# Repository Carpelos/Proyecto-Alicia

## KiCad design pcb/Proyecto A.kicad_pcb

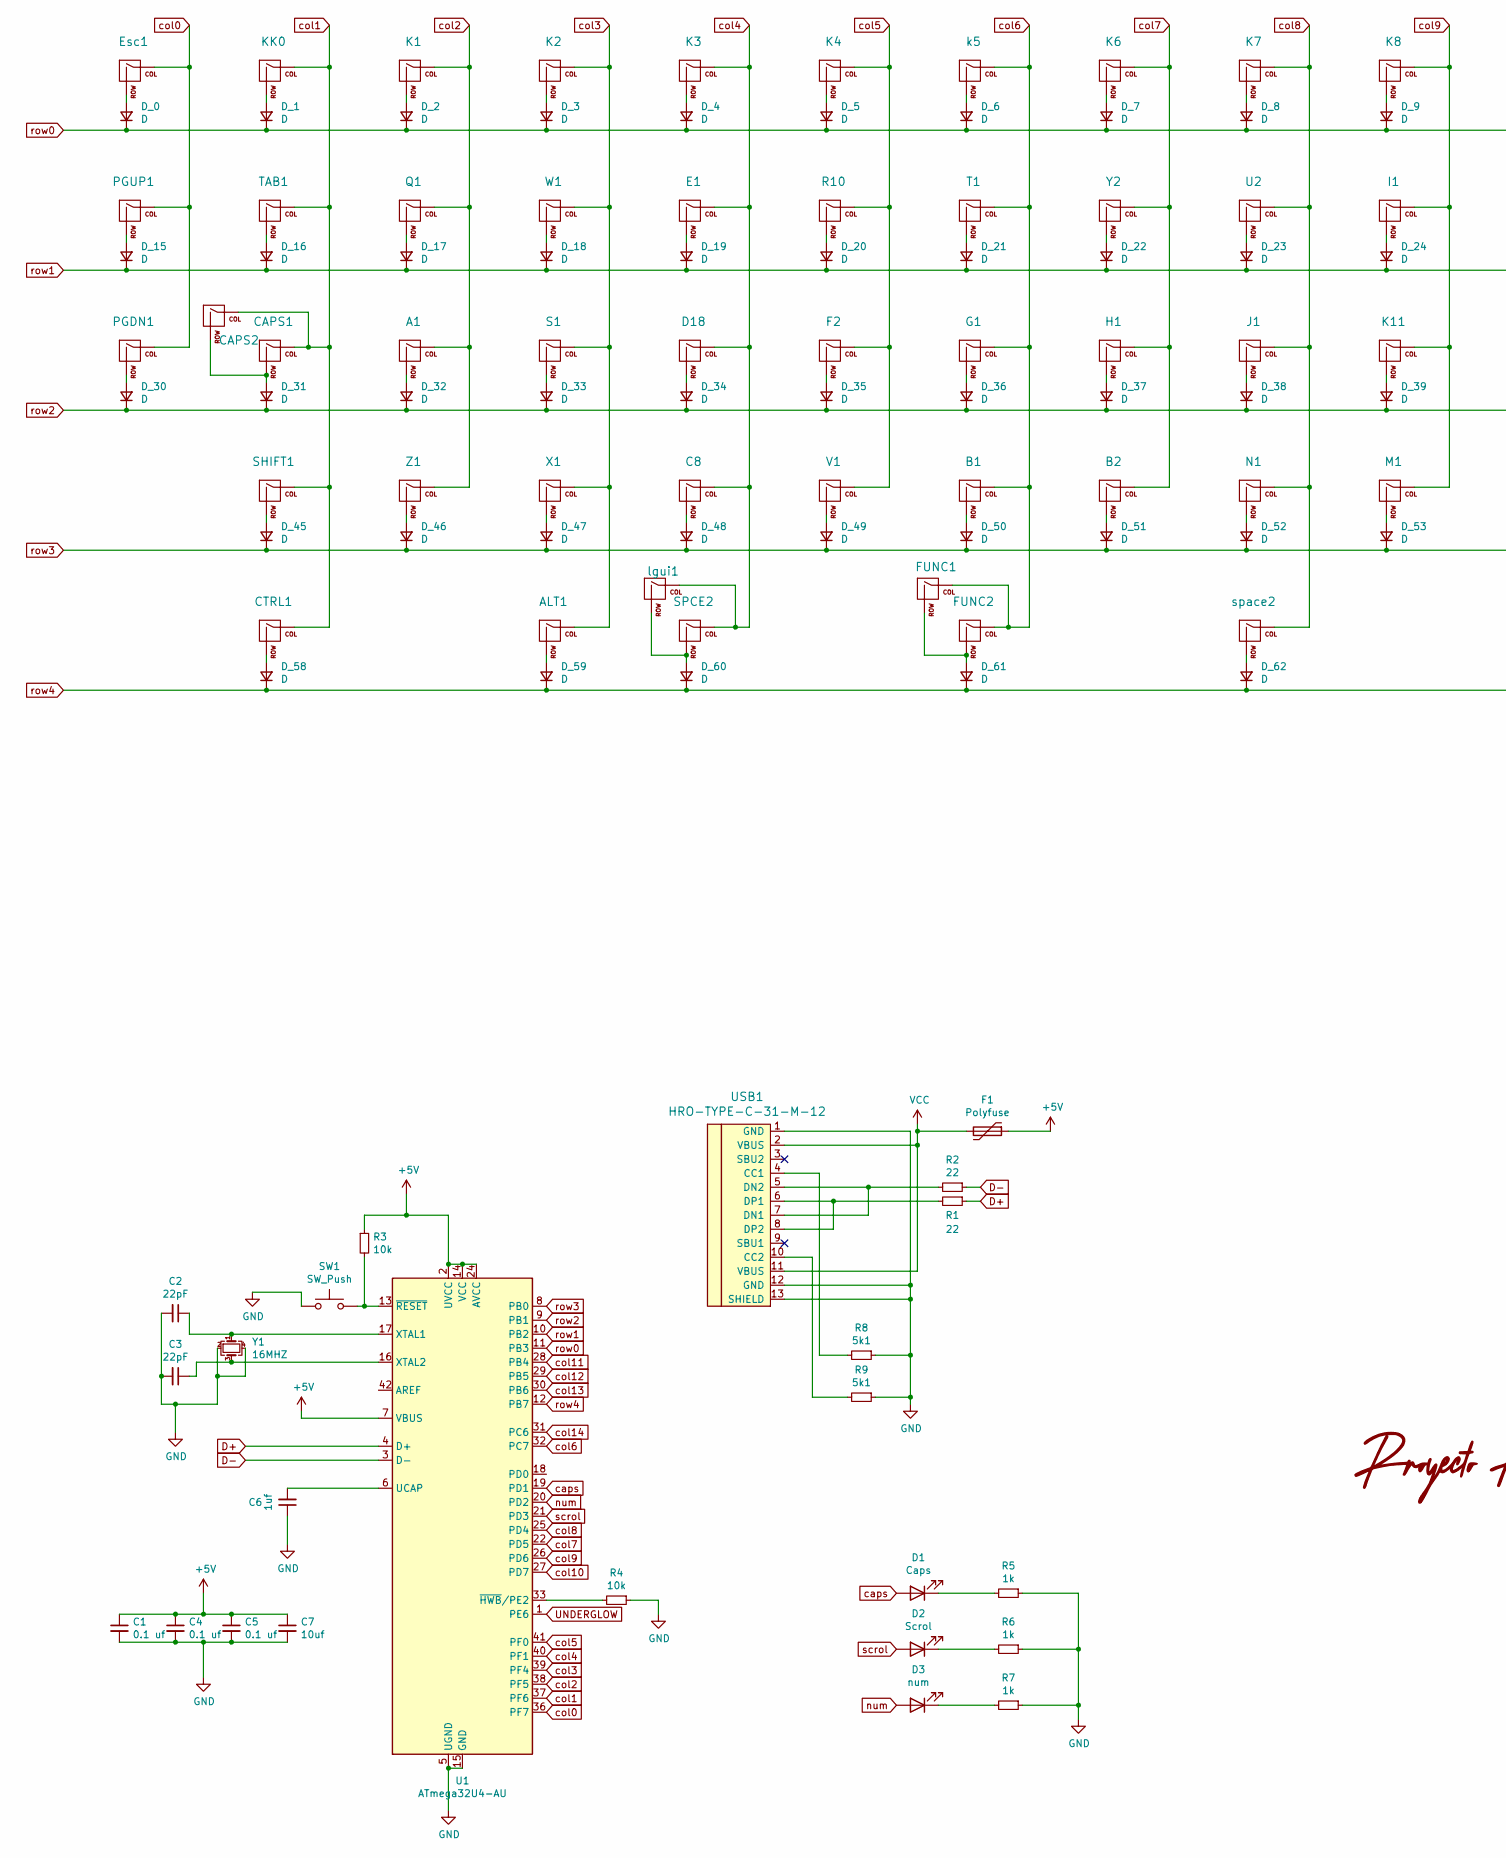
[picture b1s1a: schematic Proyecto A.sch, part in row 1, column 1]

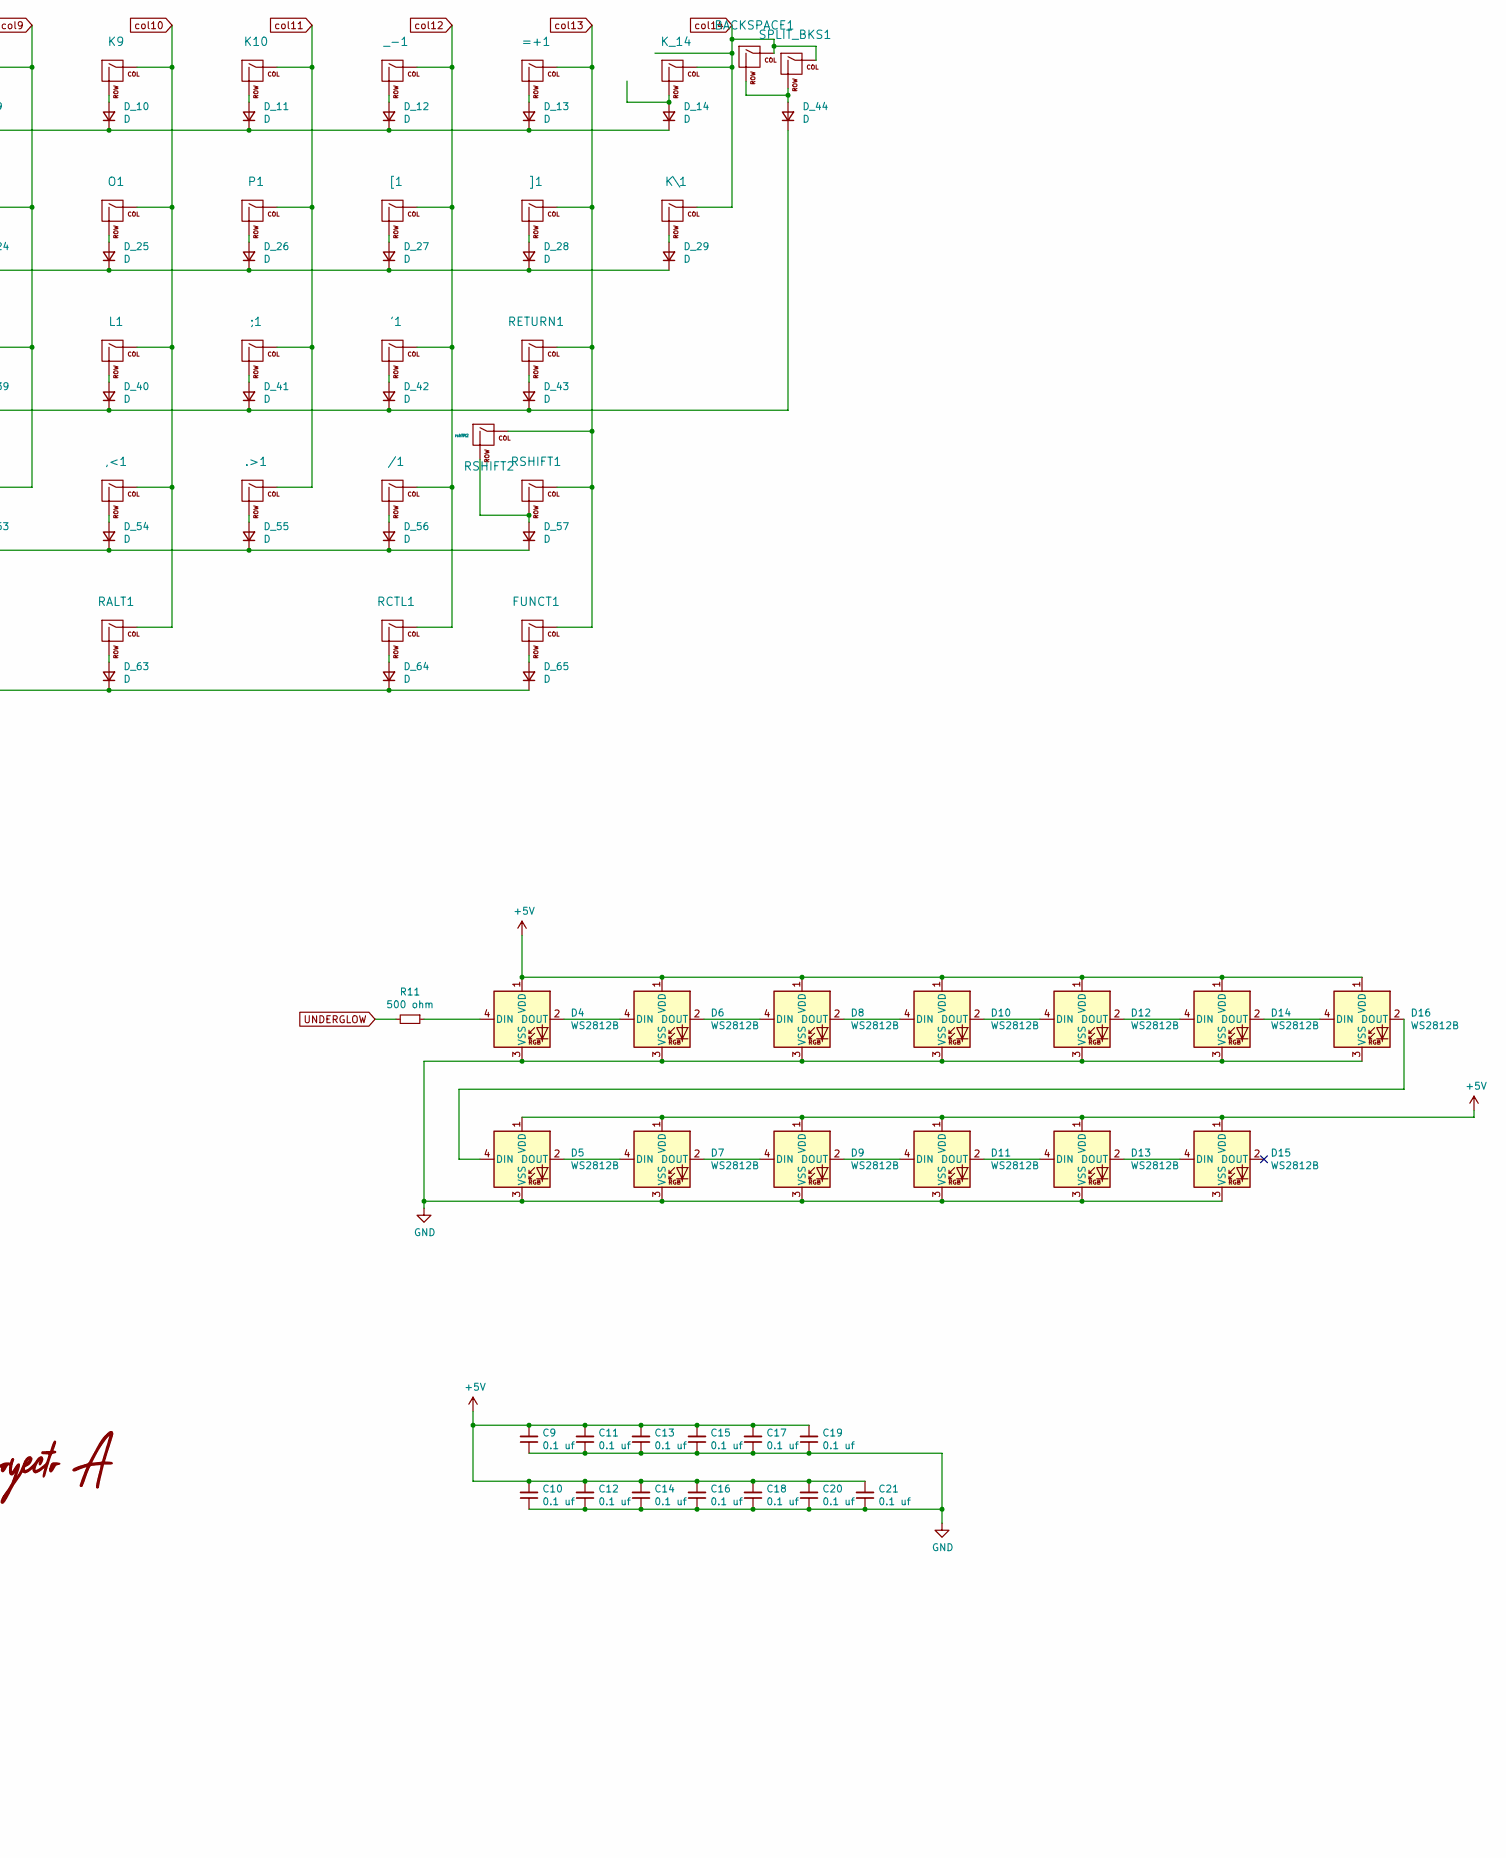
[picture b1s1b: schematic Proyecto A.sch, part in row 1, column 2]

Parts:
'1: '; MXOnly-1U-NoLED
,<1: ,<; MXOnly-1U-NoLED
.>1: .>; MXOnly-1U-NoLED
/1: /; MXOnly-1U-NoLED
;1: ;; MXOnly-1U-NoLED
=+1: =; MXOnly-1U-NoLED
A1: a; MXOnly-1U-NoLED
ALT1: lalt; MXOnly-1.5U-NoLED
B1: b; MXOnly-1U-NoLED
B2: b2; MXOnly-1U-NoLED
BACKSPACE1: backspace; MXOnly-2U-NoLED
C1, C4, C5, C9, C10, C11, C12, C13, C14, C15, C16, C17, C18, C19, C20, C21: 0.1 uf; C_0805_2012Metric_Pad1.15x1.40mm_HandSolder
C2, C3: 22pF; C_0805_2012Metric_Pad1.15x1.40mm_HandSolder
C6: 1uf; C_0805_2012Metric_Pad1.15x1.40mm_HandSolder
C7: 10uf; C_0805_2012Metric_Pad1.15x1.40mm_HandSolder
C8: c; MXOnly-1U-NoLED
CAPS1: caps1; MXOnly-1.75U-NoLED
CAPS2: stcaps; MXOnly-1U-NoLED
CTRL1: lctrl; MXOnly-1.5U-NoLED
D1: Caps; LED_1206_3216Metric_Pad1.42x1.75mm_HandSolder
D2: Scrol; LED_1206_3216Metric_Pad1.42x1.75mm_HandSolder
D3: num; LED_1206_3216Metric_Pad1.42x1.75mm_HandSolder
D4, D5, D6, D7, D8, D9, D10, D11, D12, D13, D14, D15, D16: WS2812B; LED_WS2812B_PLCC4_5.0x5.0mm_P3.2mm
D18: d; MXOnly-1U-NoLED
D_0, D_1, D_2, D_3, D_4, D_5, D_6, D_7, D_8, D_9, D_10, D_11, D_12, D_13, D_14, D_15, D_16, D_17, D_18, D_19, D_20, D_21, D_22, D_23, D_24, D_25, D_26, D_27, D_28, D_29, D_30, D_31, D_32, D_33, D_34, D_35, D_36, D_37, D_38, D_39, D_40, D_41, D_42, D_43, D_44, D_45, D_46, D_47, D_48, D_49, D_50, D_51, D_52, D_53, D_54, D_55, D_56, D_57, D_58, D_59, D_60, D_61, D_62, D_63, D_64, D_65: D; D_SOD-123; JLC C64898
E1: e; MXOnly-1U-NoLED
Esc1: KEYSW; MXOnly-1U-NoLED
F1: Polyfuse; Fuse_1206_3216Metric
F2: f; MXOnly-1U-NoLED
FUNC1: func1; MXOnly-1U-NoLED
FUNC2: func1-2; MXOnly-1.25U-NoLED
FUNCT1: FUNC3; MXOnly-1U-NoLED
G1: g; MXOnly-1U-NoLED
H1: h; MXOnly-1U-NoLED
I1: i; MXOnly-1U-NoLED
J1: j; MXOnly-1U-NoLED
K1: 1; MXOnly-1U-NoLED
K2: 2; MXOnly-1U-NoLED
K3: 3; MXOnly-1U-NoLED
K4: 4; MXOnly-1U-NoLED
K6: 6; MXOnly-1U-NoLED
K7: 7; MXOnly-1U-NoLED
K8: 8; MXOnly-1U-NoLED
K9: 9; MXOnly-1U-NoLED
K10: 10; MXOnly-1U-NoLED
K11: k; MXOnly-1U-NoLED
KK0: ES; MXOnly-1U-NoLED
K\1: \\|; MXOnly-1U-NoLED
K_14: sbackspace; MXOnly-1U-NoLED
L1: l; MXOnly-1U-NoLED
M1: KEYSW; MXOnly-1U-NoLED
N1: n; MXOnly-1U-NoLED
O1: o; MXOnly-1U-NoLED
P1: p; MXOnly-1U-NoLED
PGDN1: KEYSW; MXOnly-1U-NoLED
PGUP1: pgup; MXOnly-1U-NoLED
Q1: q; MXOnly-1U-NoLED
R1, R2: 22; R_0805_2012Metric
R3, R4: 10k; R_0805_2012Metric
R5, R6, R7: 1k; R_0805_2012Metric
R8, R9: 5k1; R_0805_2012Metric
R10: r; MXOnly-1U-NoLED
R11: 500 ohm; R_0805_2012Metric_Pad1.15x1.40mm_HandSolder
RALT1: ralt; MXOnly-1.5U-NoLED
RCTL1: RCTRL; MXOnly-1.5U-NoLED
RETURN1: return; MXOnly-2.25U-ReversedStabilizers-NoLED
RSHIFT1: rshift1; MXOnly-1.75U-NoLED
RSHIFT2: rshift2; MXOnly-2.75U-NoLED
S1: s; MXOnly-1U-NoLED
SHIFT1: lshift; MXOnly-2.25U-NoLED
SPCE2: lgui2; MXOnly-2U-ReversedStabilizers-NoLED
SPLIT_BKS1: sbbackspace2; MXOnly-1U-NoLED
SW1: SW_Push; SW_SPST_SKQG_WithStem
T1: t; MXOnly-1U-NoLED
TAB1: tabulador; MXOnly-1.5U-NoLED
U1: ATmega32U4-AU; TQFP-44_10x10mm_P0.8mm
U2: u; MXOnly-1U-NoLED
USB1: HRO-TYPE-C-31-M-12; HRO-TYPE-C-31-M-12-HandSoldering
V1: v; MXOnly-1U-NoLED
W1: w; MXOnly-1U-NoLED
X1: x; MXOnly-1U-NoLED
Y1: 16MHZ; Crystal_SMD_3225-4Pin_3.2x2.5mm_HandSoldering
Y2: y; MXOnly-1U-NoLED
Z1: z; MXOnly-1U-NoLED
[1: [; MXOnly-1U-NoLED
]1: ]; MXOnly-1U-NoLED
_-1: -; MXOnly-1U-NoLED
k5: 5; MXOnly-1U-NoLED
lgui1: lgui; MXOnly-2.25U-ReversedStabilizers-NoLED
space2: KEYSW; MXOnly-2.75U-ReversedStabilizers-NoLED

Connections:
+5V: C1.1, C4.1, C5.1, C7.1, C9.2, C10.2, C11.2, C12.2, C13.2, C14.2, C15.2, C16.2, C17.2, C18.2, C19.2, C20.2, C21.2, D4.1 (VDD), D5.1 (VDD), D6.1 (VDD), D7.1 (VDD), D8.1 (VDD), D9.1 (VDD), D10.1 (VDD), D11.1 (VDD), D12.1 (VDD), D13.1 (VDD), D14.1 (VDD), D15.1 (VDD), D16.1 (VDD), F1.1, R3.1, U1.2 (UVCC), U1.7 (VBUS), U1.14 (VCC), U1.24 (AVCC), U1.34 (VCC), U1.44 (AVCC)
D+: R1.1, U1.4 (D+)
D-: R2.1, U1.3 (D-)
GND: C1.2, C2.2, C3.2, C4.2, C5.2, C6.1, C7.2, C9.1, C10.1, C11.1, C12.1, C13.1, C14.1, C15.1, C16.1, C17.1, C18.1, C19.1, C20.1, C21.1, D4.3 (VSS), D5.3 (VSS), D6.3 (VSS), D7.3 (VSS), D8.3 (VSS), D9.3 (VSS), D10.3 (VSS), D11.3 (VSS), D12.3 (VSS), D13.3 (VSS), D14.3 (VSS), D15.3 (VSS), D16.3 (VSS), R4.1, R5.1, R6.1, R7.1, R8.1, R9.1, SW1.1, U1.5 (UGND), U1.15 (GND), U1.23 (GND), U1.35 (GND), U1.43 (GND), USB1.1 (GND), USB1.12 (GND), USB1.13 (SHIELD), Y1.2, Y1.4
unnamed: '1.2 (ROW), D_42.2 (A)
unnamed: ,<1.2 (ROW), D_54.2 (A)
unnamed: .>1.2 (ROW), D_55.2 (A)
unnamed: /1.2 (ROW), D_56.2 (A)
unnamed: ;1.2 (ROW), D_41.2 (A)
unnamed: =+1.2 (ROW), D_13.2 (A)
unnamed: A1.2 (ROW), D_32.2 (A)
unnamed: ALT1.2 (ROW), D_59.2 (A)
unnamed: B1.2 (ROW), D_50.2 (A)
unnamed: B2.2 (ROW), D_51.2 (A)
unnamed: BACKSPACE1.2 (ROW), D_44.2 (A), SPLIT_BKS1.2 (ROW)
unnamed: C2.1, U1.17 (XTAL1), Y1.1
unnamed: C3.1, U1.16 (XTAL2), Y1.3
unnamed: C6.2, U1.6 (UCAP)
unnamed: C8.2 (ROW), D_48.2 (A)
unnamed: CAPS1.2 (ROW), CAPS2.2 (ROW), D_31.2 (A)
unnamed: CTRL1.2 (ROW), D_58.2 (A)
unnamed: D1.1 (K), R5.2
unnamed: D2.1 (K), R6.2
unnamed: D3.1 (K), R7.2
unnamed: D4.2 (DOUT), D6.4 (DIN)
unnamed: D4.4 (DIN), R11.1
unnamed: D5.2 (DOUT), D7.4 (DIN)
unnamed: D6.2 (DOUT), D8.4 (DIN)
unnamed: D7.2 (DOUT), D9.4 (DIN)
unnamed: D10.2 (DOUT), D12.4 (DIN)
unnamed: D8.2 (DOUT), D10.4 (DIN)
unnamed: D11.2 (DOUT), D13.4 (DIN)
unnamed: D9.2 (DOUT), D11.4 (DIN)
unnamed: D12.2 (DOUT), D14.4 (DIN)
unnamed: D13.2 (DOUT), D15.4 (DIN)
unnamed: D14.2 (DOUT), D16.4 (DIN)
unnamed: D5.4 (DIN), D16.2 (DOUT)
unnamed: D18.2 (ROW), D_34.2 (A)
unnamed: D_0.2 (A), Esc1.2 (ROW)
unnamed: D_1.2 (A), KK0.2 (ROW)
unnamed: D_2.2 (A), K1.2 (ROW)
unnamed: D_3.2 (A), K2.2 (ROW)
unnamed: D_4.2 (A), K3.2 (ROW)
unnamed: D_5.2 (A), K4.2 (ROW)
unnamed: D_6.2 (A), k5.2 (ROW)
unnamed: D_7.2 (A), K6.2 (ROW)
unnamed: D_8.2 (A), K7.2 (ROW)
unnamed: D_9.2 (A), K8.2 (ROW)
unnamed: D_10.2 (A), K9.2 (ROW)
unnamed: D_11.2 (A), K10.2 (ROW)
unnamed: D_12.2 (A), _-1.2 (ROW)
unnamed: D_14.2 (A), K_14.2 (ROW)
unnamed: D_15.2 (A), PGUP1.2 (ROW)
unnamed: D_16.2 (A), TAB1.2 (ROW)
unnamed: D_17.2 (A), Q1.2 (ROW)
unnamed: D_18.2 (A), W1.2 (ROW)
unnamed: D_19.2 (A), E1.2 (ROW)
unnamed: D_20.2 (A), R10.2 (ROW)
unnamed: D_21.2 (A), T1.2 (ROW)
unnamed: D_22.2 (A), Y2.2 (ROW)
unnamed: D_23.2 (A), U2.2 (ROW)
unnamed: D_24.2 (A), I1.2 (ROW)
unnamed: D_25.2 (A), O1.2 (ROW)
unnamed: D_26.2 (A), P1.2 (ROW)
unnamed: D_27.2 (A), [1.2 (ROW)
unnamed: D_28.2 (A), ]1.2 (ROW)
unnamed: D_29.2 (A), K\1.2 (ROW)
unnamed: D_30.2 (A), PGDN1.2 (ROW)
unnamed: D_33.2 (A), S1.2 (ROW)
unnamed: D_35.2 (A), F2.2 (ROW)
unnamed: D_36.2 (A), G1.2 (ROW)
unnamed: D_37.2 (A), H1.2 (ROW)
unnamed: D_38.2 (A), J1.2 (ROW)
unnamed: D_39.2 (A), K11.2 (ROW)
unnamed: D_40.2 (A), L1.2 (ROW)
unnamed: D_43.2 (A), RETURN1.2 (ROW)
unnamed: D_45.2 (A), SHIFT1.2 (ROW)
unnamed: D_46.2 (A), Z1.2 (ROW)
unnamed: D_47.2 (A), X1.2 (ROW)
unnamed: D_49.2 (A), V1.2 (ROW)
unnamed: D_52.2 (A), N1.2 (ROW)
unnamed: D_53.2 (A), M1.2 (ROW)
unnamed: D_57.2 (A), RSHIFT1.2 (ROW), RSHIFT2.2 (ROW)
unnamed: D_60.2 (A), SPCE2.2 (ROW), lgui1.2 (ROW)
unnamed: D_61.2 (A), FUNC1.2 (ROW), FUNC2.2 (ROW)
unnamed: D_62.2 (A), space2.2 (ROW)
unnamed: D_63.2 (A), RALT1.2 (ROW)
unnamed: D_64.2 (A), RCTL1.2 (ROW)
unnamed: D_65.2 (A), FUNCT1.2 (ROW)
unnamed: R1.2, USB1.6 (DP1), USB1.8 (DP2)
unnamed: R2.2, USB1.5 (DN2), USB1.7 (DN1)
unnamed: R3.2, SW1.2, U1.13 (~RESET)
unnamed: R4.2, U1.33 (~HWB~/PE2)
unnamed: R8.2, USB1.4 (CC1)
unnamed: R9.2, USB1.10 (CC2)
UNDERGLOW: R11.2, U1.1 (PE6)
VCC: F1.2, USB1.2 (VBUS), USB1.11 (VBUS)
caps: D1.2 (A), U1.19 (PD1)
col0: Esc1.1 (COL), PGDN1.1 (COL), PGUP1.1 (COL), U1.36 (PF7)
col1: CAPS1.1 (COL), CAPS2.1 (COL), CTRL1.1 (COL), KK0.1 (COL), SHIFT1.1 (COL), TAB1.1 (COL), U1.37 (PF6)
col2: A1.1 (COL), K1.1 (COL), Q1.1 (COL), U1.38 (PF5), Z1.1 (COL)
col3: ALT1.1 (COL), K2.1 (COL), S1.1 (COL), U1.39 (PF4), W1.1 (COL), X1.1 (COL)
col4: C8.1 (COL), D18.1 (COL), E1.1 (COL), K3.1 (COL), SPCE2.1 (COL), U1.40 (PF1), lgui1.1 (COL)
col5: F2.1 (COL), K4.1 (COL), R10.1 (COL), U1.41 (PF0), V1.1 (COL)
col6: B1.1 (COL), FUNC1.1 (COL), FUNC2.1 (COL), G1.1 (COL), T1.1 (COL), U1.32 (PC7), k5.1 (COL)
col7: B2.1 (COL), H1.1 (COL), K6.1 (COL), U1.22 (PD5), Y2.1 (COL)
col8: J1.1 (COL), K7.1 (COL), N1.1 (COL), U1.25 (PD4), U2.1 (COL), space2.1 (COL)
col9: I1.1 (COL), K8.1 (COL), K11.1 (COL), M1.1 (COL), U1.26 (PD6)
col10: ,<1.1 (COL), K9.1 (COL), L1.1 (COL), O1.1 (COL), RALT1.1 (COL), U1.27 (PD7)
col11: .>1.1 (COL), ;1.1 (COL), K10.1 (COL), P1.1 (COL), U1.28 (PB4)
col12: '1.1 (COL), /1.1 (COL), RCTL1.1 (COL), U1.29 (PB5), [1.1 (COL), _-1.1 (COL)
col13: =+1.1 (COL), FUNCT1.1 (COL), RETURN1.1 (COL), RSHIFT1.1 (COL), RSHIFT2.1 (COL), U1.30 (PB6), ]1.1 (COL)
col14: BACKSPACE1.1 (COL), K\1.1 (COL), K_14.1 (COL), SPLIT_BKS1.1 (COL), U1.31 (PC6)
num: D3.2 (A), U1.20 (PD2)
row0: D_0.1 (K), D_1.1 (K), D_2.1 (K), D_3.1 (K), D_4.1 (K), D_5.1 (K), D_6.1 (K), D_7.1 (K), D_8.1 (K), D_9.1 (K), D_10.1 (K), D_11.1 (K), D_12.1 (K), D_13.1 (K), D_14.1 (K), U1.11 (PB3)
row1: D_15.1 (K), D_16.1 (K), D_17.1 (K), D_18.1 (K), D_19.1 (K), D_20.1 (K), D_21.1 (K), D_22.1 (K), D_23.1 (K), D_24.1 (K), D_25.1 (K), D_26.1 (K), D_27.1 (K), D_28.1 (K), D_29.1 (K), U1.10 (PB2)
row2: D_30.1 (K), D_31.1 (K), D_32.1 (K), D_33.1 (K), D_34.1 (K), D_35.1 (K), D_36.1 (K), D_37.1 (K), D_38.1 (K), D_39.1 (K), D_40.1 (K), D_41.1 (K), D_42.1 (K), D_43.1 (K), D_44.1 (K), U1.9 (PB1)
row3: D_45.1 (K), D_46.1 (K), D_47.1 (K), D_48.1 (K), D_49.1 (K), D_50.1 (K), D_51.1 (K), D_52.1 (K), D_53.1 (K), D_54.1 (K), D_55.1 (K), D_56.1 (K), D_57.1 (K), U1.8 (PB0)
row4: D_58.1 (K), D_59.1 (K), D_60.1 (K), D_61.1 (K), D_62.1 (K), D_63.1 (K), D_64.1 (K), D_65.1 (K), U1.12 (PB7)
scrol: D2.2 (A), U1.21 (PD3)

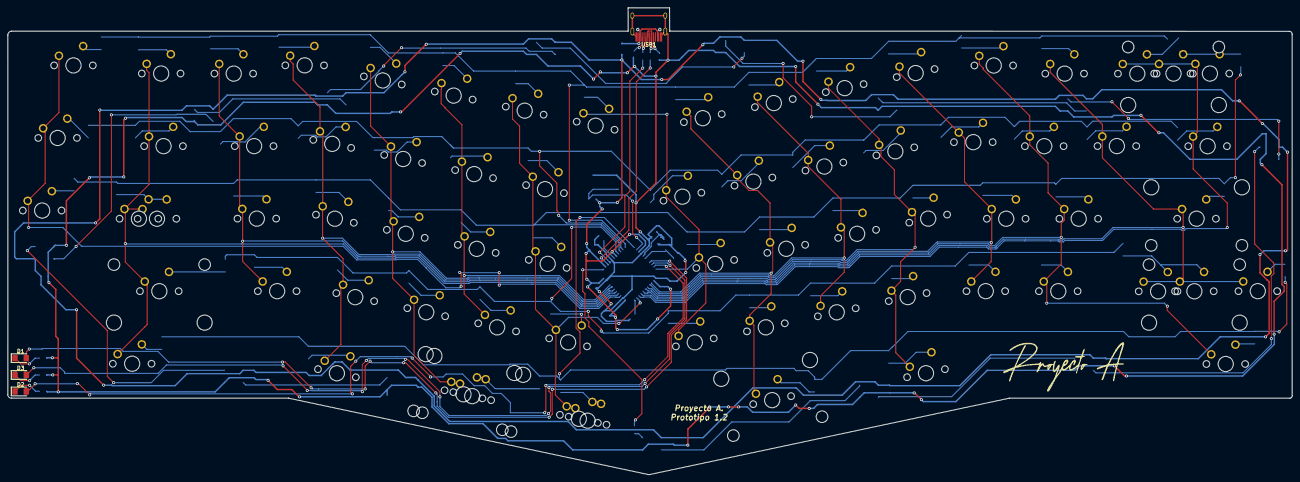
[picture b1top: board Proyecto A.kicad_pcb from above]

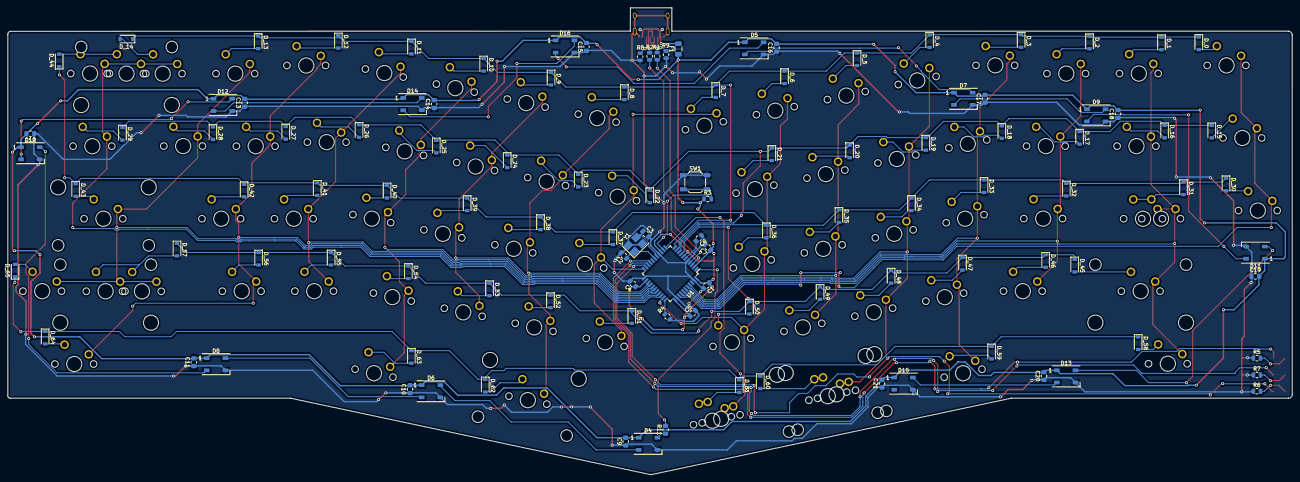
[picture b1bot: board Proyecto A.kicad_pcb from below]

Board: 2 copper layers, 337.3 x 122.6 mm, 188 parts (113 on the bottom side), 120 nets.

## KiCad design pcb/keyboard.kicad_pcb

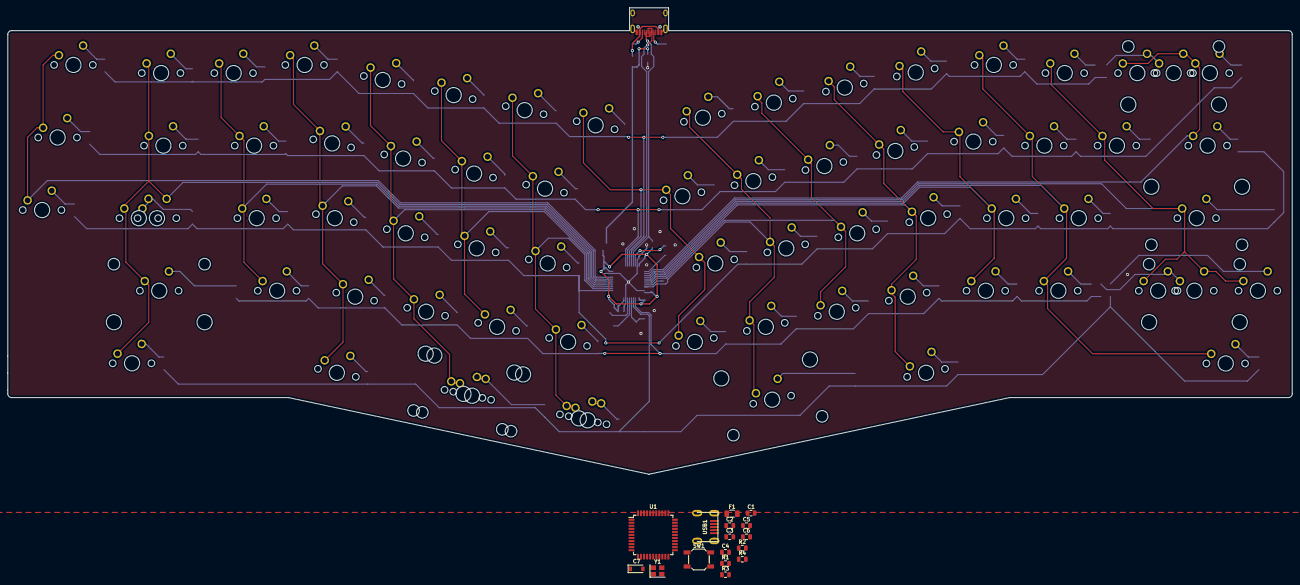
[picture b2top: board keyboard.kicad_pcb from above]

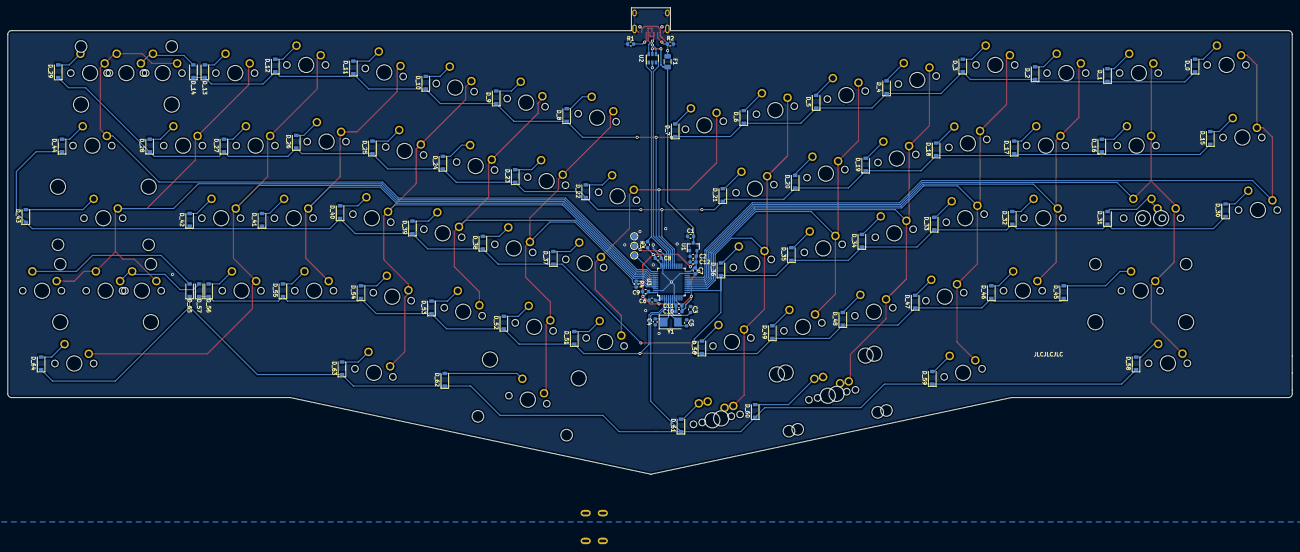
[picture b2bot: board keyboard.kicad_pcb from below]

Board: 2 copper layers, 337.2 x 122.5 mm, 178 parts (90 on the bottom side), 108 nets.

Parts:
C1, C4, C5: 0.1 uf; C_0805_2012Metric
C1#2, C2#2, C10: 1u; C_0603_1608Metric
C2, C3: 22pF; C_0805_2012Metric
C3#2, C6#2, C7#2, C8, C9, C11: 100n; C_0603_1608Metric
C4#2, C5#2: 20p; C_0603_1608Metric
C6: C_Small; C_0805_2012Metric
C7: 100uf; D_SOD-123
C12: 10u; C_0603_1608Metric
D_0, D_1, D_2, D_3, D_4, D_5, D_6, D_7, D_8, D_9, D_10, D_11, D_12, D_13, D_14, D_15, D_16, D_17, D_18, D_19, D_20, D_21, D_22, D_23, D_24, D_25, D_26, D_27, D_28, D_29, D_30, D_31, D_32, D_33, D_34, D_35, D_36, D_37, D_38, D_39, D_40, D_41, D_42, D_43, D_44, D_45, D_46, D_47, D_48, D_49, D_50, D_51, D_52, D_53, D_54, D_55, D_56, D_57, D_58, D_59, D_60, D_61, D_62, D_63, D_64, D_65: D; D_SOD-123
F1: Polyfuse; Fuse_1206_3216Metric
F1#2: 500mA; Fuse_1206_3216Metric
J1, J2, J3: Conn_01x01_Female; TestPoint_Pad_D1.5mm
K_0, K_1, K_2, K_3, K_4, K_5, K_6, K_7, K_8, K_9, K_10, K_11, K_12, K_13, K_14, K_15, K_17, K_18, K_19, K_20, K_21, K_22, K_23, K_24, K_25, K_26, K_27, K_28, K_29, K_30, K_32, K_33, K_34, K_35, K_36, K_37, K_38, K_39, K_40, K_41, K_42, K_46, K_47, K_48, K_49, K_50, K_51, K_52, K_53, K_54, K_55, K_56, K_65: KEYSW; MXOnly-1U-NoLED
K_16, K_44, K_58, K_59, K_63, K_64: KEYSW; MXOnly-1.5U-NoLED
K_31, K_57: KEYSW; MXOnly-1.75U-NoLED
K_43: KEYSW; MXOnly-2.25U-ReversedStabilizers-NoLED
K_45: KEYSW; MXOnly-2.25U-NoLED
K_60: KEYSW; MXOnly-2U-ReversedStabilizers-NoLED
K_61: KEYSW; MXOnly-1.25U-NoLED
K_62: KEYSW; MXOnly-2.75U-ReversedStabilizers-NoLED
K_142: MX-NoLED; MXOnly-2U-NoLED
K_312, K_612: MX-NoLED; MXOnly-1U-NoLED
K_572: MX-NoLED; MXOnly-2.75U-NoLED
K_602: MX-NoLED; MXOnly-2.25U-ReversedStabilizers-NoLED
R1, R2: 22; Fuse_0805_2012Metric
R1#2, R2#2: 5.1k; R_0603_1608Metric
R3: R_Small; Fuse_0805_2012Metric
R3#2: 1.5k; R_0603_1608Metric
R4: 10k; Fuse_0805_2012Metric
R4#2: 10k; R_0603_1608Metric
SW1: SW_Push; SW_SPST_SKQG_WithStem
U1: ATmega32U4-AU; TQFP-44_10x10mm_P0.8mm
U1#2: XC6206P332MR; SOT-23
U2: SRV05-4; SOT-23-6
U3: STM32F103C8Tx; LQFP-48_7x7mm_P0.5mm
USB1: Molex-0548190589
USB1#2: HRO-TYPE-C-31-M-12; HRO-TYPE-C-31-M-12-jlc
Y1: 16MHZ; Crystal_SMD_3225-4Pin_3.2x2.5mm
Y1#2: 8MHz; Crystal_SMD_5032-2Pin_5.0x3.2mm

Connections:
+5V: C1.1, C1#2.2, C4.1, C5.1, C7.1, F1.1, F1#2.1, R3.1, U1.2, U1.7, U1.14, U1.24, U1.34, U1.44, U1#2.3, U2.5
/VBUS: F1#2.2, USB1#2.2, USB1#2.11
BOOT0: R4#2.1, U3.44
D+: R2.2, R3#2.2, U2.6, U3.33, USB1.3, USB1#2.6, USB1#2.8
D-: R1.2, U2.4, U3.32, USB1.4, USB1#2.5, USB1#2.7
GND: C1.2, C1#2.1, C2.2, C2#2.2, C3.2, C3#2.2, C4.2, C4#2.2, C5.2, C5#2.2, C6.1, C6#2.2, C7.2, C7#2.2, C8.2, C9.2, C10.2, C11.2, C12.2, J3.1, R1#2.1, R2#2.1, R4.1, R4#2.2, SW1.1, U1.5, U1.15, U1.23, U1.35, U1.43, U1#2.1, U2.2, U3.8, U3.23, U3.35, U3.47, USB1.1, USB1#2.1, USB1#2.12, USB1#2.13, Y1.2, Y1.4
NRST: C3#2.1, U3.7
unnamed: C2.1, U1.17, Y1.1
unnamed: C3.1, U1.16, Y1.3
unnamed: C4#2.1, U3.5, Y1#2.1
unnamed: C5#2.1, U3.6, Y1#2.2
unnamed: C6.2, U1.6
unnamed: D_0.2, K_0.2
unnamed: D_1.2, K_1.2
unnamed: D_2.2, K_2.2
unnamed: D_3.2, K_3.2
unnamed: D_4.2, K_4.2
unnamed: D_5.2, K_5.2
unnamed: D_6.2, K_6.2
unnamed: D_7.2, K_7.2
unnamed: D_8.2, K_8.2
unnamed: D_9.2, K_9.2
unnamed: D_10.2, K_10.2
unnamed: D_11.2, K_11.2
unnamed: D_12.2, K_12.2
unnamed: D_13.2, K_13.2
unnamed: D_14.2, K_14.2, K_142.1
unnamed: D_15.2, K_15.2
unnamed: D_16.2, K_16.2
unnamed: D_17.2, K_17.2
unnamed: D_18.2, K_18.2
unnamed: D_19.2, K_19.2
unnamed: D_20.2, K_20.2
unnamed: D_21.2, K_21.2
unnamed: D_22.2, K_22.2
unnamed: D_23.2, K_23.2
unnamed: D_24.2, K_24.2
unnamed: D_25.2, K_25.2
unnamed: D_26.2, K_26.2
unnamed: D_27.2, K_27.2
unnamed: D_28.2, K_28.2
unnamed: D_29.2, K_29.2
unnamed: D_30.2, K_30.2
unnamed: D_31.2, K_31.2, K_312.1
unnamed: D_32.2, K_32.2
unnamed: D_33.2, K_33.2
unnamed: D_34.2, K_34.2
unnamed: D_35.2, K_35.2
unnamed: D_36.2, K_36.2
unnamed: D_37.2, K_37.2
unnamed: D_38.2, K_38.2
unnamed: D_39.2, K_39.2
unnamed: D_40.2, K_40.2
unnamed: D_41.2, K_41.2
unnamed: D_42.2, K_42.2
unnamed: D_43.2, K_43.2
unnamed: D_44.2, K_44.2
unnamed: D_45.2, K_45.2
unnamed: D_46.2, K_46.2
unnamed: D_47.2, K_47.2
unnamed: D_48.2, K_48.2
unnamed: D_49.2, K_49.2
unnamed: D_50.2, K_50.2
unnamed: D_51.2, K_51.2
unnamed: D_52.2, K_52.2
unnamed: D_53.2, K_53.2
unnamed: D_54.2, K_54.2
unnamed: D_55.2, K_55.2
unnamed: D_56.2, K_56.2
unnamed: D_57.2, K_57.2, K_572.1
unnamed: D_58.2, K_58.2
unnamed: D_59.2, K_59.2
unnamed: D_60.2, K_60.2, K_602.2
unnamed: D_61.2, K_61.2, K_612.2
unnamed: D_62.2, K_62.2
unnamed: D_63.2, K_63.2
unnamed: D_64.2, K_64.2
unnamed: D_65.2, K_65.2
unnamed: R1.1, U1.3
unnamed: R1#2.2, USB1#2.4
unnamed: R2.1, U1.4
unnamed: R2#2.2, USB1#2.10
unnamed: R3.2, SW1.2, U1.13
unnamed: R4.2, U1.33
SWDCLK: J2.1, U3.37
SWDIO: J1.1, U3.34
VBAT: C2#2.1, C6#2.1, C7#2.1, C8.1, C9.1, C10.1, C11.1, C12.1, R3#2.1, U1#2.2, U3.1, U3.9, U3.24, U3.36, U3.48
VCC: F1.2, USB1.5
col0: K_0.1, K_15.1, K_30.1, U3.21
col1: K_1.1, K_16.1, K_31.1, K_45.1, K_58.1, K_312.2, U3.20
col2: K_2.1, K_17.1, K_32.1, K_46.1, U3.19
col3: K_3.1, K_18.1, K_33.1, K_47.1, K_59.1, U3.18
col4: K_4.1, K_19.1, K_34.1, K_48.1, K_60.1, K_602.1, U3.17
col5: K_5.1, K_20.1, K_35.1, K_49.1, U3.16
col6: K_6.1, K_21.1, K_36.1, K_50.1, K_61.1, K_612.1, U3.15
col7: K_7.1, K_22.1, K_37.1, K_51.1, U3.30
col8: K_8.1, K_23.1, K_38.1, K_52.1, K_62.1, U3.45
col9: K_9.1, K_24.1, K_39.1, K_53.1, U3.43
col10: K_10.1, K_25.1, K_40.1, K_54.1, K_63.1, U3.42
col11: K_11.1, K_26.1, K_41.1, K_55.1, U3.41
col12: K_12.1, K_27.1, K_42.1, K_56.1, K_64.1, U3.40
col13: K_13.1, K_28.1, K_43.1, K_57.1, K_65.1, K_572.2, U3.39
col14: K_14.1, K_29.1, K_44.1, K_142.2, U3.38
row0: D_0.1, D_1.1, D_2.1, D_3.1, D_4.1, D_5.1, D_6.1, D_7.1, D_8.1, D_9.1, D_10.1, D_11.1, D_12.1, D_13.1, D_14.1, U3.31
row1: D_15.1, D_16.1, D_17.1, D_18.1, D_19.1, D_20.1, D_21.1, D_22.1, D_23.1, D_24.1, D_25.1, D_26.1, D_27.1, D_28.1, D_29.1, U3.29
row2: D_30.1, D_31.1, D_32.1, D_33.1, D_34.1, D_35.1, D_36.1, D_37.1, D_38.1, D_39.1, D_40.1, D_41.1, D_42.1, D_43.1, D_44.1, U3.14
row3: D_45.1, D_46.1, D_47.1, D_48.1, D_49.1, D_50.1, D_51.1, D_52.1, D_53.1, D_54.1, D_55.1, D_56.1, D_57.1, U1.36, U3.3
row4: D_58.1, D_59.1, D_60.1, D_61.1, D_62.1, D_63.1, D_64.1, D_65.1, U1.37, U3.4

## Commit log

2020-07-18 Inicial
2020-07-18 added a 500 ohm resistor bettween mcu underglow pin and 1st ws2812b
2020-07-27 Proto 1.1
2020-07-28 proto 1.2
    Moved usb to top side of the pcb
2020-08-05 Acrylic Case updated
2020-08-09 updated plate.
2020-08-10 qmk firmware
2020-08-29 Caja acrílica y cambios en la PCB
